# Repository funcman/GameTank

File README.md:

GameTank是由Clyde Shaffer研制的一款八位开源游戏机。

本项目fork自[GameTank硬件原始项目](https://github.com/clydeshaffer/gametank)，作为我对GameTank进行学习、制造、游戏开发的一个综合的库。

一开始，我将使用[KiCad](https://www.kicad.or/)比照者原始实现，重绘GameTank硬件的电路原理图和PCB设计图，这是个学习过程。

Just for Fun!

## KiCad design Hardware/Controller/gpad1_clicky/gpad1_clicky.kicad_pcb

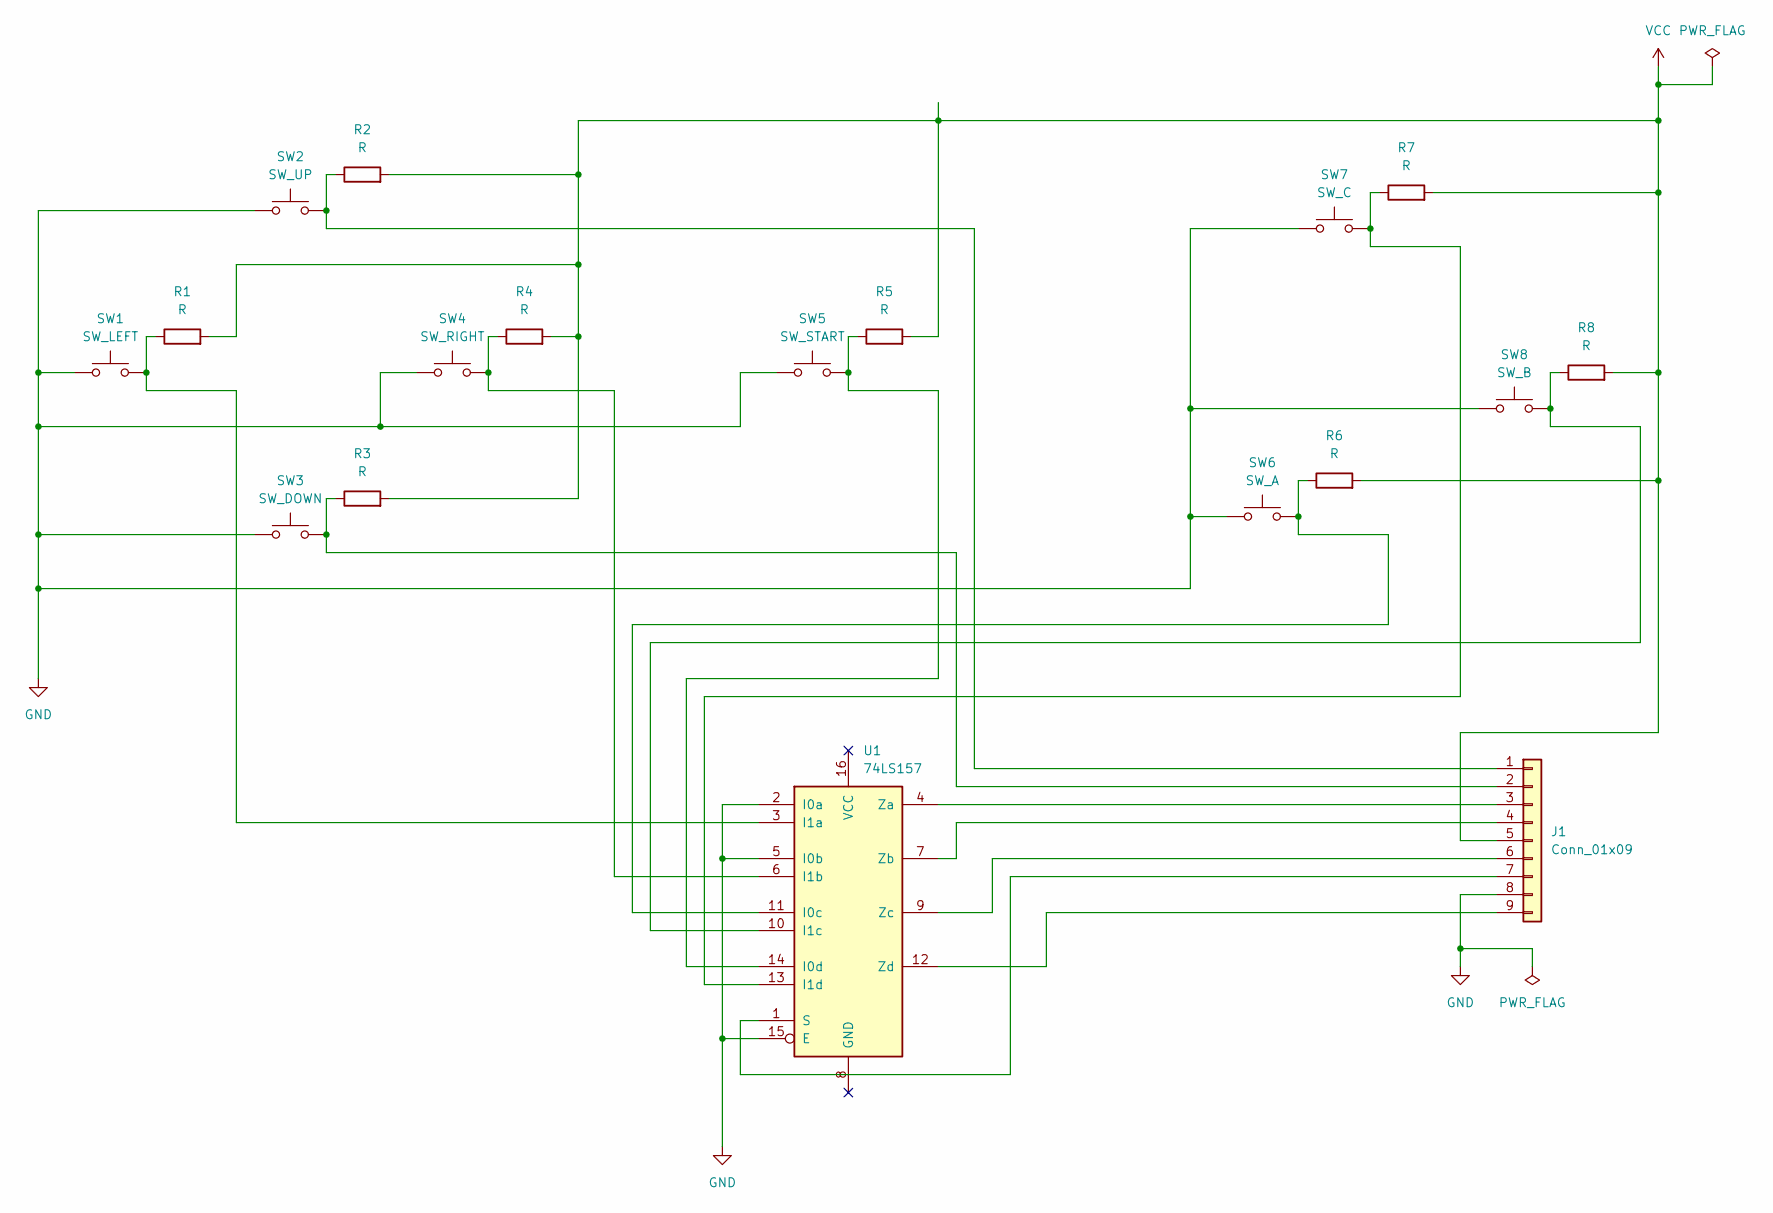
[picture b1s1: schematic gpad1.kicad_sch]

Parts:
J1: Conn_01x09; PinHeader_1x09_P2.54mm_Horizontal
R1, R2, R3, R4, R5, R6, R7, R8: R; R_Axial_DIN0207_L6.3mm_D2.5mm_P10.16mm_Horizontal
SW1: SW_LEFT; SW_Cherry_MX_1.00u_PCB
SW2: SW_UP; SW_Cherry_MX_1.00u_PCB
SW3: SW_DOWN; SW_Cherry_MX_1.00u_PCB
SW4: SW_RIGHT; SW_Cherry_MX_1.00u_PCB
SW5: SW_START; SW_Cherry_MX_1.00u_PCB
SW6: SW_A; SW_Cherry_MX_1.00u_PCB
SW7: SW_C; SW_Cherry_MX_1.00u_PCB
SW8: SW_B; SW_Cherry_MX_1.00u_PCB
U1: 74LS157; DIP-16_W7.62mm

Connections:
GND: J1.8, SW1.1, SW2.1, SW3.1, SW4.1, SW5.1, SW6.1, SW7.1, SW8.1, U1.2 (I0a), U1.5 (I0b), U1.15 (E)
unnamed: J1.1, R2.1, SW2.2
unnamed: J1.2, R3.1, SW3.2
unnamed: J1.3, U1.4 (Za)
unnamed: J1.4, U1.7 (Zb)
unnamed: J1.6, U1.9 (Zc)
unnamed: J1.7, U1.1 (S)
unnamed: J1.9, U1.12 (Zd)
unnamed: R1.1, SW1.2, U1.3 (I1a)
unnamed: R4.1, SW4.2, U1.6 (I1b)
unnamed: R5.1, SW5.2, U1.14 (I0d)
unnamed: R6.1, SW6.2, U1.11 (I0c)
unnamed: R7.1, SW7.2, U1.13 (I1d)
unnamed: R8.1, SW8.2, U1.10 (I1c)
VCC: J1.5, R1.2, R2.2, R3.2, R4.2, R5.2, R6.2, R7.2, R8.2

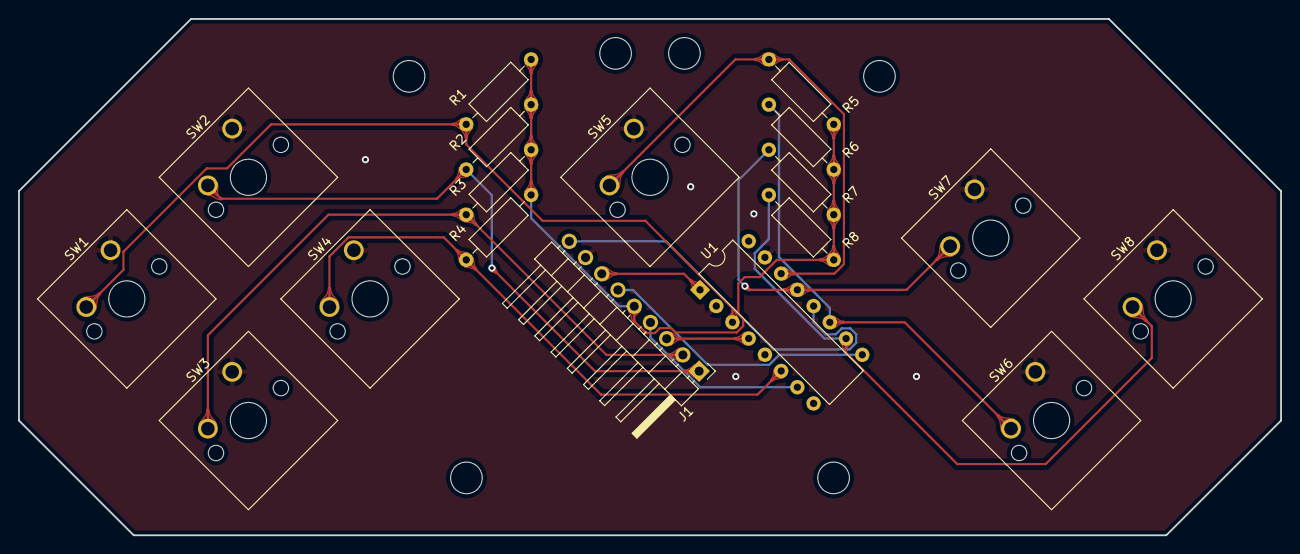
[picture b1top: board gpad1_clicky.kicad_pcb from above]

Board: 2 copper layers, 139.7 x 57.1 mm, 18 parts (0 on the bottom side), 15 nets.

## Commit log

2023-02-11 My first commit, add readme
2023-02-11 Kick my ass... fix the extname
2023-02-11 Add game pad kicad files
